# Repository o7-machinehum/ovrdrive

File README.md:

# Ovrdrive

Ovrdrive is a purpose built security focused usb drive. If the user doesn't plug it in three times rapidly, the drive it will appear completely blank. It is entirely open source and all the tools used to build it are open source. 

## Getting this Code
I've added quite a bit of git lfs content, I will eventually remove all this, but for now you probably don't want to check this out. You can do so like this

    GIT_LFS_SKIP_SMUDGE=1 git clone git@github.com:o7-machinehum/ovrdrive.git

## Content
 - [Blog Post](https://interruptlabs.ca/2022/07/29/I-m-Building-a-Self-Destructing-USB-Drive/)
 - [YouTube Content](https://youtu.be/Wrcy6ySjSu8)
 - [Buy in my Shop](https://shop.rootkitlabs.com/products/ovrdrive-usb)

## Firmware
```
cd fw
make deploy
```

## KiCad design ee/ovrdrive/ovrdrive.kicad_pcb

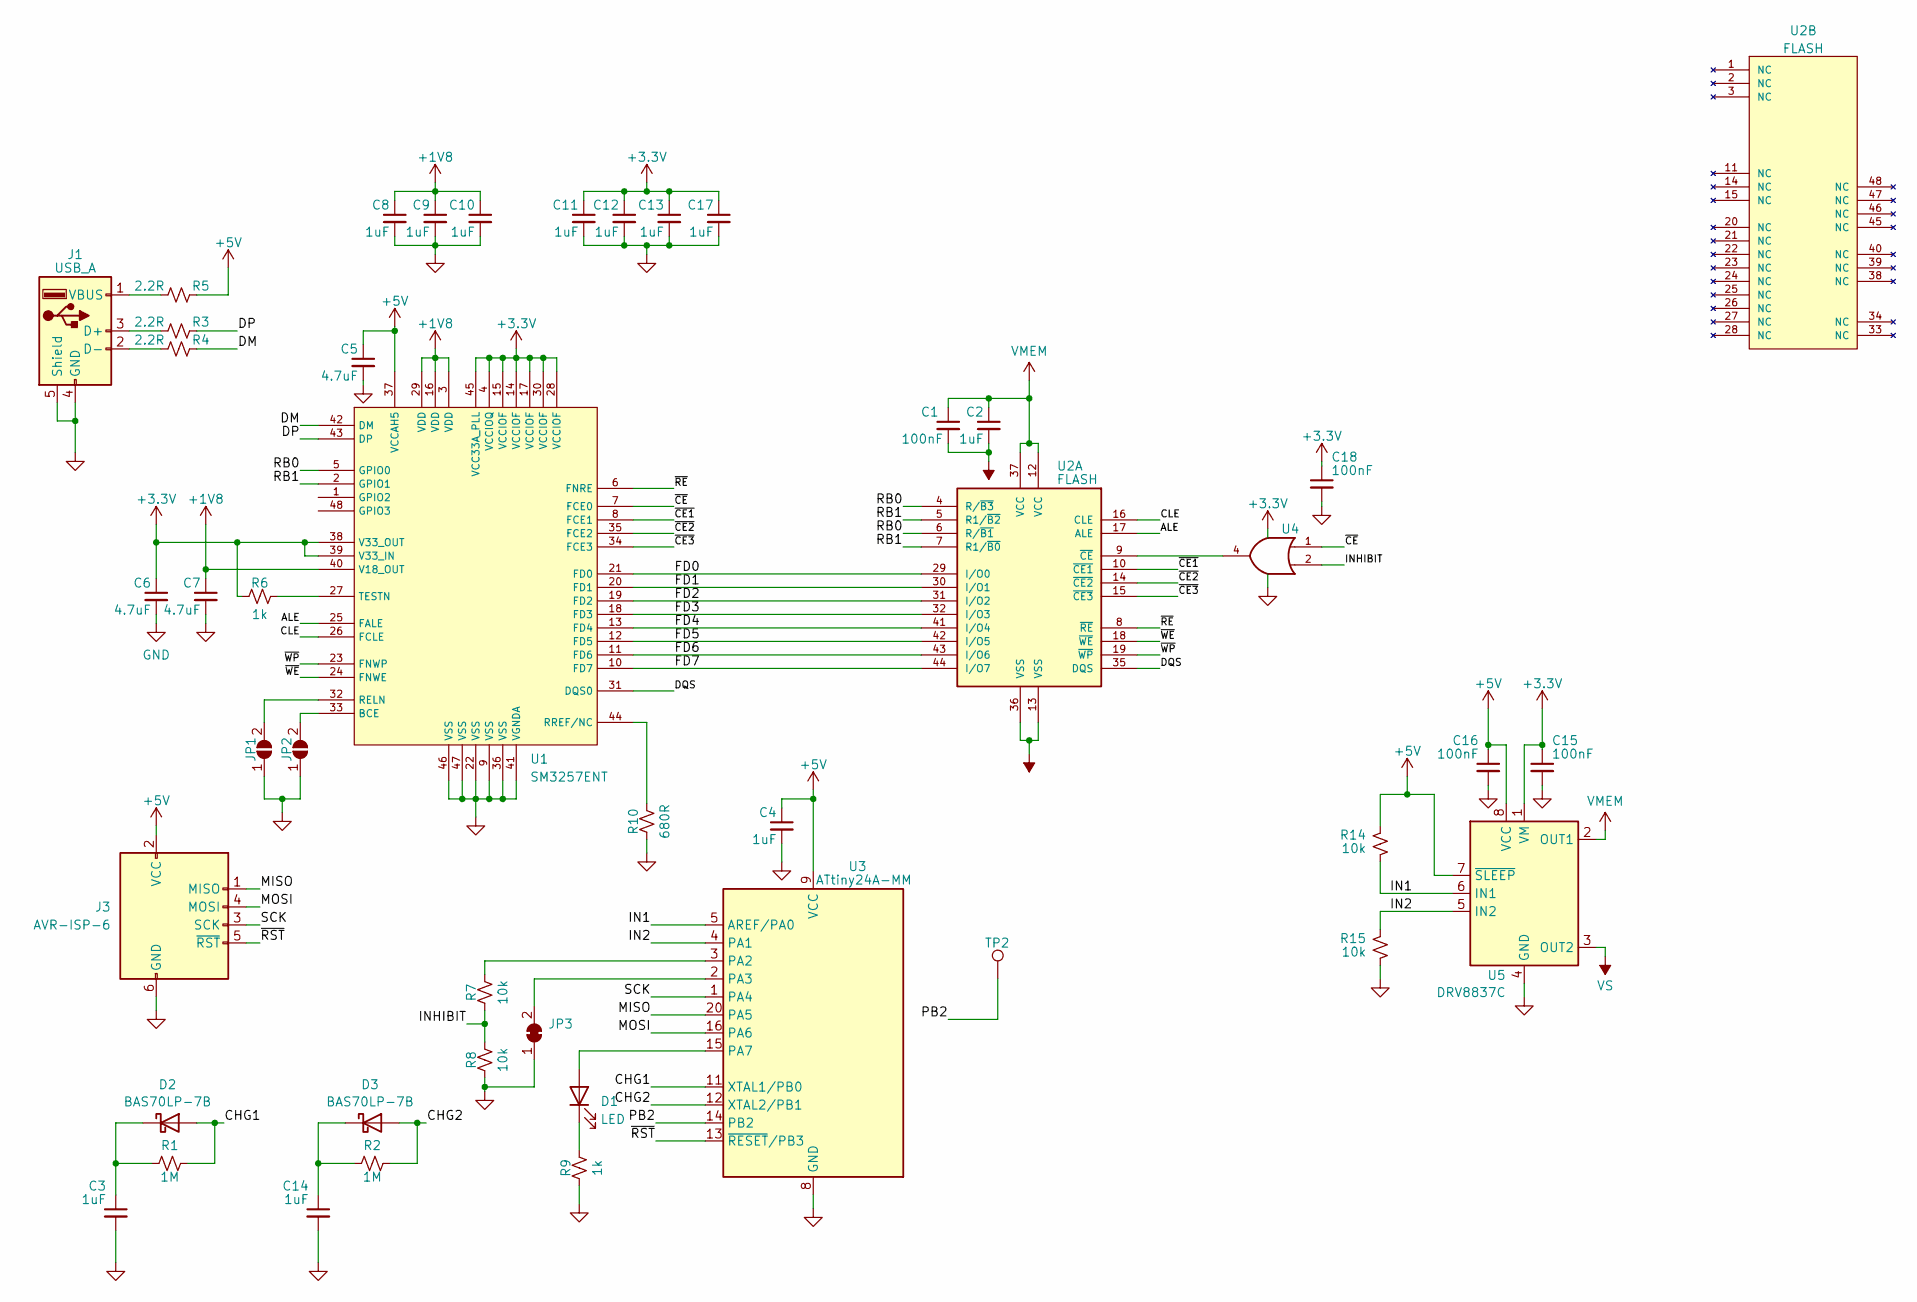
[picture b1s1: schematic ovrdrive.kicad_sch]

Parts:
C1, C15, C16, C18: 100nF; C_0603_1608Metric; MPN CC0603KRX7R7BB104
C2, C4, C8, C9, C10, C11, C12, C13, C17: 1uF; C_0603_1608Metric; MPN CC0603KRX7R7BB105
C3, C14: 1uF; C_0603_1608Metric
C5, C6, C7: 4.7uF; C_0603_1608Metric; MPN CL10A475KP8NNNC
D1: LED; LED_0603_1608Metric; MPN XZMG53W-1
D2, D3: BAS70LP-7B; D_0402_1005Metric; MPN BAS70LP-7B
J1: USB_A; USB_A_CNCTech_1001-011-01101_Horizontal; MPN 0480372200
J3: AVR-ISP-6; PinHeader_2x03_P1.27mm_Horizontal; MPN 20021112-00006T4LF
JP1, JP2: SolderJumper_2_Open; SolderJumper-2_P1.3mm_Open_Pad1.0x1.5mm
JP3: SolderJumper_2_Bridged; SolderJumper-2_P1.3mm_Bridged2Bar_RoundedPad1.0x1.5mm
R1, R2: 1M; R_0402_1005Metric; MPN RC0402FR-071ML
R3, R4, R5: 2.2R; R_0603_1608Metric; MPN RC0603FR-072R2L
R6: 1k; R_0603_1608Metric; MPN RC0603FR-071KL
R7, R8: 10k; R_0402_1005Metric; MPN RC0402FR-0710KL
R9: 1k; R_0402_1005Metric; MPN RC0402FR-071KL
R10: 680R; R_0603_1608Metric; MPN RC0603FR-07680RL
R14, R15: 10k; R_0603_1608Metric; MPN RC0402FR-0710KL
TP2: TestPoint; TestPoint_Pad_D1.0mm
U1: SM3257ENT; TQFP-48_7x7mm_P0.5mm; MPN SM3257ENT
U2: FLASH; tsop48; MPN K9HDG08U1A
U3: ATtiny24A-MM; QFN-20-1EP_3x3mm_P0.45mm_EP1.6x1.6mm; MPN ATTINY24A-MMHR
U4: SN74LVC1G32DCKR; SOT-353_SC-70-5; MPN SN74LVC1G32DCKR
U5: DRV8837C; WSON-8-1EP_2x2mm_P0.5mm_EP0.9x1.6mm; MPN DRV8837CDSGR

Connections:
+1V8: C7.1, C8.1, C9.1, C10.1, U1.3 (VDD), U1.16 (VDD), U1.29 (VDD), U1.40 (V18_OUT)
+3.3V: C6.1, C11.1, C12.1, C13.1, C15.1, C17.1, C18.1, R6.1, U1.4 (VCCIOQ), U1.14 (VCCIOF), U1.15 (VCCIOF), U1.17 (VCCIOF), U1.28 (VCCIOF), U1.30 (VCCIOF), U1.38 (V33_OUT), U1.39 (V33_IN), U1.45 (VCC33A_PLL), U4.5 (VCC), U5.1 (VM)
+5V: C4.1, C5.1, C16.1, J3.2 (VCC), R5.2, R14.2, U1.37 (VCCAH5), U3.9 (VCC), U5.7 (~SLEEP), U5.8 (VCC)
/ALE: U1.25 (FALE), U2.17 (ALE)
/CHG1: D2.2 (A), R1.1, U3.11 (XTAL1/PB0)
/CHG2: D3.2 (A), R2.1, U3.12 (XTAL2/PB1)
/CLE: U1.26 (FCLE), U2.16 (CLE)
/DM: R4.2, U1.42 (DM)
/DP: R3.2, U1.43 (DP)
/DQS: U1.31 (DQS0), U2.35 (DQS)
/FD0: U1.21 (FD0), U2.29 (I/O0)
/FD1: U1.20 (FD1), U2.30 (I/O1)
/FD2: U1.19 (FD2), U2.31 (I/O2)
/FD3: U1.18 (FD3), U2.32 (I/O3)
/FD4: U1.13 (FD4), U2.41 (I/O4)
/FD5: U1.12 (FD5), U2.42 (I/O5)
/FD6: U1.11 (FD6), U2.43 (I/O6)
/FD7: U1.10 (FD7), U2.44 (I/O7)
/IN1: R14.1, U3.5 (AREF/PA0), U5.6 (IN1)
/IN2: R15.2, U3.4 (PA1), U5.5 (IN2)
/INHIBIT: R7.1, R8.2, U4.2
/MISO: J3.1 (MISO), U3.20 (PA5)
/MOSI: J3.4 (MOSI), U3.16 (PA6)
/PB2: TP2.1, U3.14 (PB2)
/RB0: U1.5 (GPIO0), U2.4 (R/~B3), U2.6 (R/~B1)
/RB1: U1.2 (GPIO1), U2.5 (R1/~B2), U2.7 (R1/~B0)
/SCK: J3.3 (SCK), U3.1 (PA4)
/~CE1: U1.8 (FCE1), U2.10 (~CE1)
/~CE2: U1.35 (FCE2), U2.14 (~CE2)
/~CE3: U1.34 (FCE3), U2.15 (~CE3)
/~CE: U1.7 (FCE0), U4.1
/~RE: U1.6 (FNRE), U2.8 (~RE)
/~RST: J3.5 (~RST), U3.13 (~RESET/PB3)
/~WE: U1.24 (FNWE), U2.18 (~WE)
/~WP: U1.23 (FNWP), U2.19 (~WP)
GND: C3.2, C4.2, C5.2, C6.2, C7.2, C8.2, C9.2, C10.2, C11.2, C12.2, C13.2, C14.2, C15.2, C16.2, C17.2, C18.2, J1.4 (GND), J1.5 (Shield), J3.6 (GND), JP1.1 (A), JP2.1 (A), JP3.1 (A), R8.1, R9.1, R10.1, R15.1, U1.9 (VSS), U1.22 (VSS), U1.36 (VSS), U1.41 (VGNDA), U1.46 (VSS), U1.47 (VSS), U3.8 (GND), U3.21 (GND), U4.3 (GND), U5.4 (GND), U5.9 (GND)
unnamed: D1.2 (A), U3.15 (PA7)
unnamed: D1.1 (K), R9.2
unnamed: C3.1, D2.1 (K), R1.2
unnamed: C14.1, D3.1 (K), R2.2
unnamed: J1.3 (D+), R3.1
unnamed: J1.2 (D-), R4.1
unnamed: J1.1 (VBUS), R5.1
unnamed: JP1.2 (B), U1.32 (RELN)
unnamed: JP2.2 (B), U1.33 (BCE)
unnamed: JP3.2 (B), U3.2 (PA3)
unnamed: R10.2, U1.44 (RREF/NC)
unnamed: R6.2, U1.27 (TESTN)
unnamed: U2.9 (~CE), U4.4
unnamed: R7.2, U3.3 (PA2)
VMEM: C1.1, C2.1, U2.12 (VCC), U2.37 (VCC), U5.2 (OUT1)
VS: C1.2, C2.2, U2.13 (VSS), U2.36 (VSS), U5.3 (OUT2)

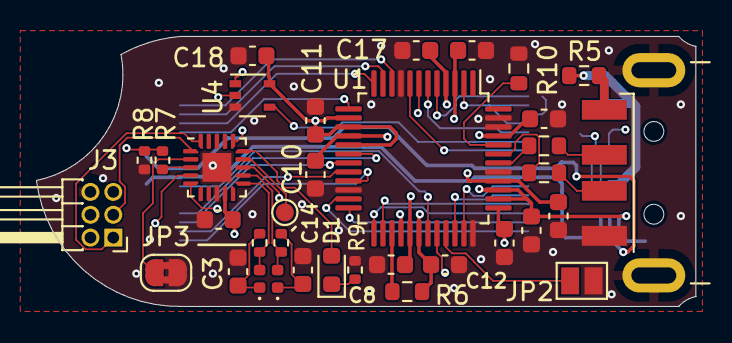
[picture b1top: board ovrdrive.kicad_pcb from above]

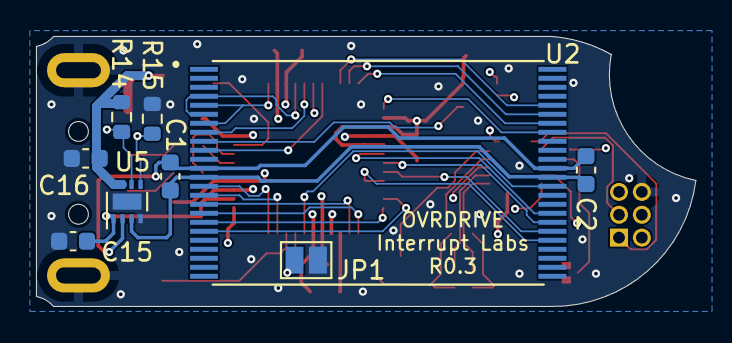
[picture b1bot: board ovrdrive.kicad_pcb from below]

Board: 4 copper layers, 36.6 x 15.0 mm, 44 parts (9 on the bottom side), 52 nets.

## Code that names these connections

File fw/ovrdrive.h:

/* Production Variables */
#define SAFE false // Don't ARM FSD cct. ?

/* IN1 / IN2 DRV8837C */
#define PIN_IN1 PA0
#define DDR_IN1 DDRA
#define PORT_IN1 PORTA
#define PIN_IN2 PA1
#define DDR_IN2 DDRA
#define PORT_IN2 PORTA

/* Flash Inhibit Signal */
#define PIN_INHIBIT PA2
#define DDR_INHIBIT DDRA
#define PORT_INHIBIT PORTA

/* LED */
#define PIN_LED PA7
#define DDR_LED DDRA
#define PORT_LED PORTA

/* Charge Pins*/
#define PIN_CHG1 PB0
#define PIN_CHG2 PB1
#define DDR_CHG DDRB
#define PORT_CHG PORTB
#define PORT_I_CHG PINB

/* Full Self Destruct Select */
#define PIN_FSD PA3
#define DDR_FSD DDRA
#define PORT_FSD PORTA
#define PORT_I_FSD PINA

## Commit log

2020-08-28 Updated the pitch deck
2020-09-01 Worked on the pitch
2022-07-19 Dropped the hardware in the initial project.
2022-07-20 Working on the board.
2022-07-20 Updated image
2022-07-20 updated image agian
2022-07-29 readme edits
2022-08-16 Updated the sm3257en to the correct pinout. Dropped some parts on the layout.
2022-08-16 Added the datasheet for the MCU, modified the gitignore and readme stuff.
2022-08-16 Added the intial firmware.
2022-08-23 Added the firmware
2022-08-23 Added design guides.
2022-08-23 Changes gitignore
2022-08-24 converted dos2unix CR's
2022-08-24 Removed some whitespace, and the code is working.
2022-09-13 Added a bunch of mech parts.
2022-09-13 Mech looking decent, new USB to fit in case.
2022-09-27 Fit seems to be working.
2022-09-27 Readme edit
2022-09-27 Added a simulation
2022-09-27 Added a dxf I forgot
2022-09-28 Routed out the power.
2022-09-29 Working on the routing.
2022-10-10 Routed out the datalines.
2022-10-18 Initial routing complete.
2022-10-18 R0.1 released
2022-11-26 Added some part numbers.
2022-11-26 Added some leftover simulations. Dunno what they are.
2022-11-26 Moved files to bench folder (breadboard) and ff folder (actual device).
2022-11-26 Undid -F placement that was placed for debugging.
2023-01-08 More readme changes.
2023-02-17 Added some datasheets made some changes to the boards.
2023-03-07 Removed analog circuitry for spit detection, shortened entire board by 0.6mm to fit in enclosure.
2023-04-06 Changes components and a leftover commit.
2023-05-02 Added R0.2 docs
2023-06-07 Added lfs files.
2023-07-07 Removed old notes files.
2023-07-07 Added a bunch of loose files laying around.
2023-07-07 Removed some strange text.
2023-07-07 Cleaned up
2023-08-01 Added config files that are working for the new flash.
2023-08-01 Change the destruction circuit to an H-bridge.
2023-08-01 Cleaned up the firmware
2023-08-01 Added screen captures of V1 destruction circuit
2023-08-01 Started the routing the new H-bridge.
2023-08-02 R0.3 released
2023-08-02 Updated the mech, added some small dimensions to the pcb.
2023-10-16 Leftover uncommited stuff.
2023-11-03 Added BOM commmited leftover stuff.
2023-11-06 Updated everything to R3.
2023-11-06 Added test scripts.
2023-11-08 Moved files around.
2023-11-08 Added some media.
2023-12-06 Added license
2023-12-11 Released R0.4 for *quote only*. Still need to do a final revision before sending off.
2023-12-11 Added new part numbers
2024-01-11 R0.41 released.
2024-04-01 fw-r1.0 release candidate
2024-04-01 Modified board size to fit enclosure better.
2024-04-01 R0.42 released, ready for review.
2024-04-01 Leftover bits
2024-04-01 Removed media from changes. To be entirely removed soon
2024-04-01 Added a linting file, linted code.
2024-05-06 Added some testing scripts
2024-05-06 Working (single thread)
2024-05-06 Runs in parallel now
2024-06-25 R1 Released! Going to production.
2024-06-25 Rebase
2024-07-01 Added the paper manual.
2024-07-01 Added makefile
2024-07-01 Added sticker tex file.
2024-07-01 Added firmware release + deploy script.
2024-07-03 Fixed French accent not showing up, took the QR code off the front of the package and moved to the manual.
2024-07-20 Removed the stickers and manual.
2024-08-28 Added a firmware readme file.
2024-08-28 Cleanup.
